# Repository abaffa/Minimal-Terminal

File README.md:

# Baffa Terminal (minimal-terminal clone) 

This is a Simple Terminal board based on "Minimal-Terminal" project by Carsten Herting (oct/2021 https://github.com/slu4coder/Minimal-Terminal).

Current version supports US-International keyboard mapping, four basic serial speeds (115200, 57600, 38400, 9600 BPS) and [supports some basic CSI/Ansi escapes](supported_escapes.md).
 
The prototype board has been tested with my CP/M machine (see http://baffa-2.baffasoft.com.br) but there is another board compatible with RC2014 pinout. 

### Video

## Baffa-2 Terminal Board:

[Order Baffa-2 Minimal Terminal PCB from PCBWay](https://www.pcbway.com/project/shareproject/Baffa_2_Minimal_Terminal_f85704c4.html)

## RC2014 Minimal-Terminal Module

[Order RC2014 Minimal Terminal PCB from PCBWay](https://www.pcbway.com/project/shareproject/RC2014_Minimal_Terminal_41593f8c.html)

## Bill of Materials

| Qty | Value | Parts | Description |
|:---:|:----------:|:-----|:-----|
| 1 |  PINHD-1X20 | JP4 |  PIN HEADER |
| 1 |  PINHD-1X40 | JP3 |  PIN HEADER |
| 6 |  100nf | C2, C6, C9, C10, C11, C12 | CAPACITOR |
| 2 |  10k | R10, R16 | RESISTOR |
| 1 | 150 | R13 | RESISTOR |
| 2 |  1k | R11, R12 | RESISTOR |
| 1 |  24Mhz XTAL |  XTAL |  XTAL SOCKET-14 |
| 1 |  330nf | C1 | CAPACITOR |
| 1 |  47uf | C7 | POLARIZED CAPACITOR |
| 1 |  74HC166N |  IC2 |  8-bit parallel load SHIFT REGISTER |
| 2 | 75 | R14, R15 | RESISTOR, American symbol |
| 1 |  7806T | IC1 |  Positive VOLTAGE REGULATOR |
| 2 |  ATMEGA328P-PU | UART_PS2, VGA |  PDIP-28 Atmel |
| 1 |  BUS UART | JP2 |  JUMPER |
| 1 |  MINI-DIN6PTH |  PS2_DIN |  mini DIN 6 Connector |
| 1 |  Power 9-12v | JP1 |  PIN HEADER |
| 1 |  RESET | S5 | MOM SWITCH |
| 1 |  SPEED | JP7 |  JUMPER |
| 1 | PINHD-1X6 | UART |  PIN HEADER |
| 1 | PINHD-1X6 |  VGA |  PIN HEADER |
| 1 | DSUB | VGA Output | SUB-D |
 
## License

Copyright (c) 2021 Augusto Baffa, Carsten Herting

Permission is hereby granted, free of charge, to any person obtaining a copy
of this software and associated documentation files (the "Software"), to deal
in the Software without restriction, including without limitation the rights
to use, copy, modify, merge, publish, distribute, sublicense, and/or sell
copies of the Software, and to permit persons to whom the Software is
furnished to do so, subject to the following conditions:

The above copyright notice and this permission notice shall be included in all
copies or substantial portions of the Software.

THE SOFTWARE IS PROVIDED "AS IS", WITHOUT WARRANTY OF ANY KIND, EXPRESS OR
IMPLIED, INCLUDING BUT NOT LIMITED TO THE WARRANTIES OF MERCHANTABILITY,
FITNESS FOR A PARTICULAR PURPOSE AND NONINFRINGEMENT. IN NO EVENT SHALL THE
AUTHORS OR COPYRIGHT HOLDERS BE LIABLE FOR ANY CLAIM, DAMAGES OR OTHER
LIABILITY, WHETHER IN AN ACTION OF CONTRACT, TORT OR OTHERWISE, ARISING FROM,
OUT OF OR IN CONNECTION WITH THE SOFTWARE OR THE USE OR OTHER DEALINGS IN THE
SOFTWARE.

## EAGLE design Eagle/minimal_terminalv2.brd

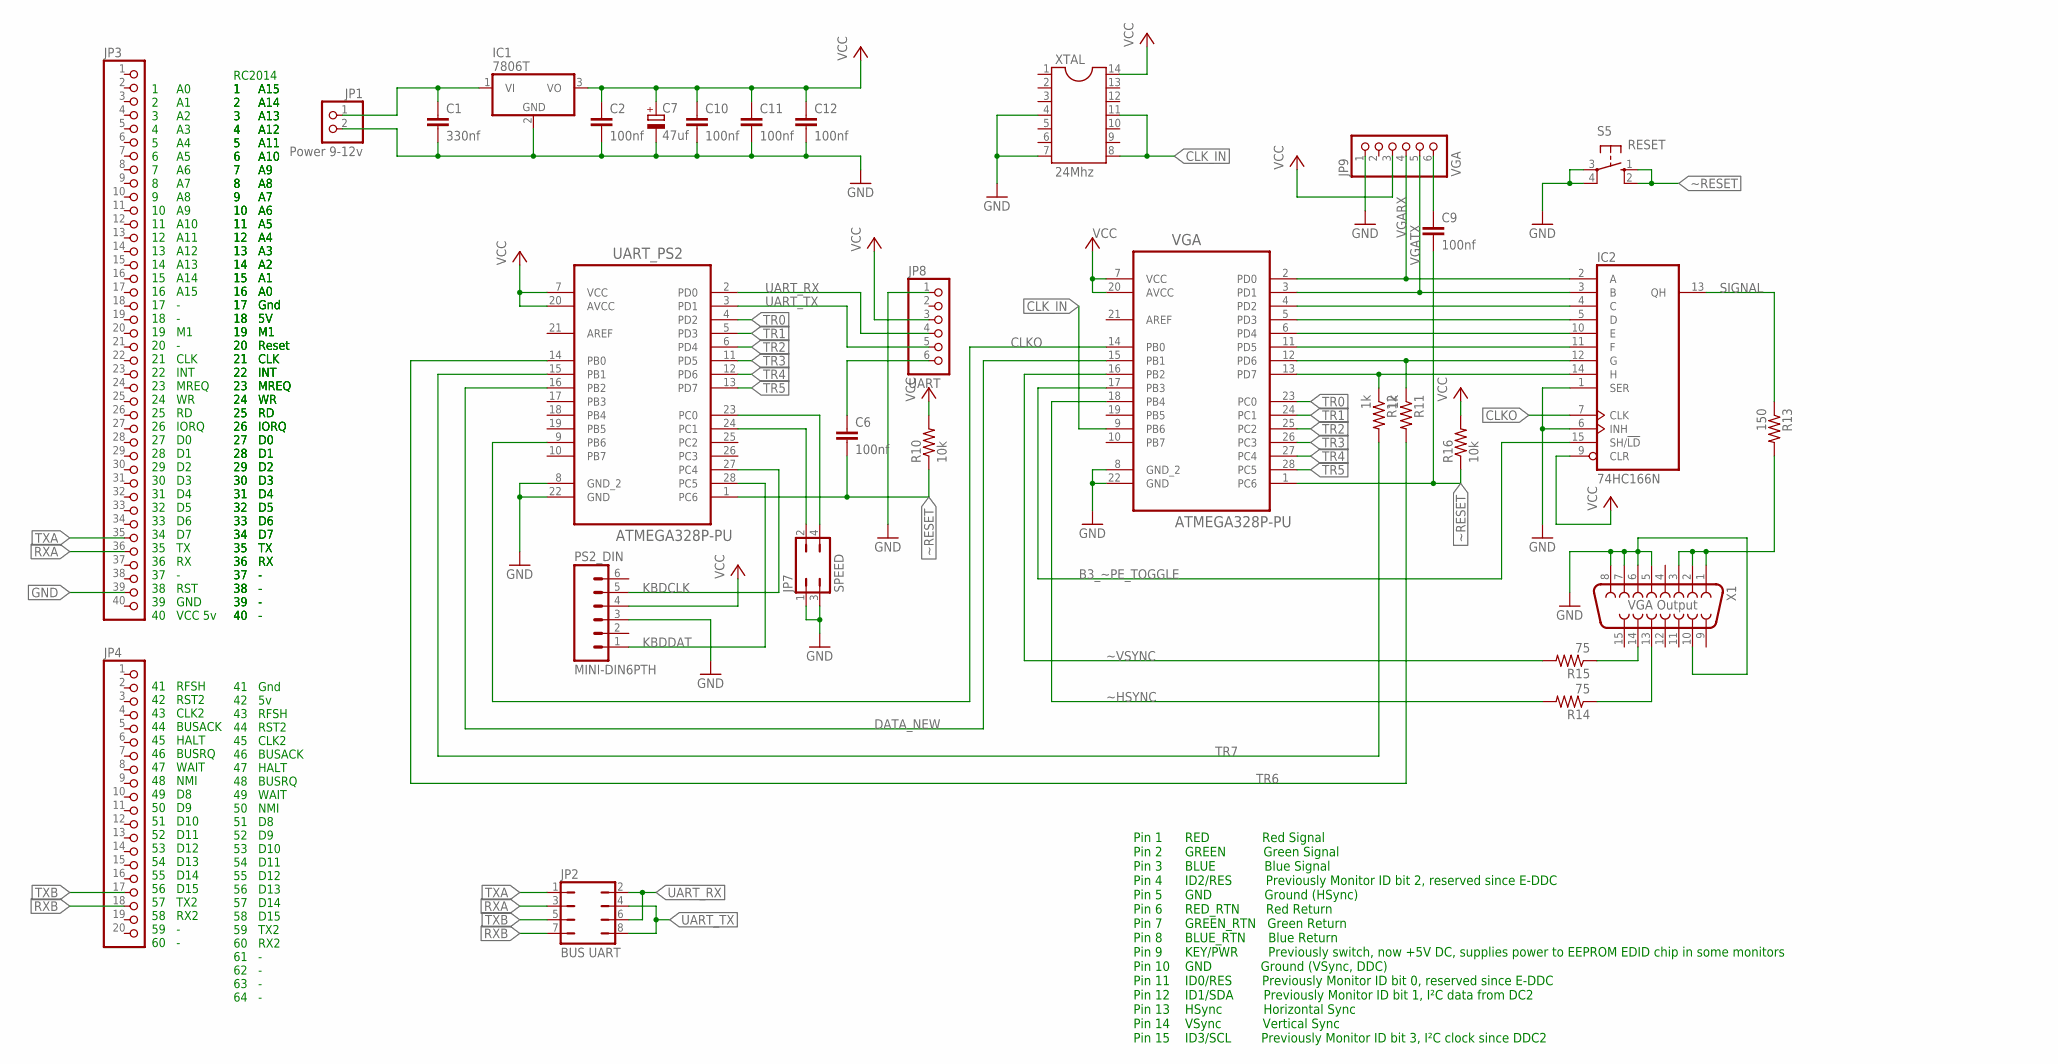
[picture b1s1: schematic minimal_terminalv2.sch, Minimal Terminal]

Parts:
C1: 330nf; C2.5-3
C2, C6, C9, C10, C11, C12: 100nf; C2.5-3
C7: 47uf; E2,5-6
IC1: 7806T; TO220H
IC2: 74HC166N; DIL16
JP1: Power 9-12v; 1X02
JP2: BUS UART; JP4Q
JP3: PINHD-1X40; 1X40
JP4: PINHD-1X20; 1X20
JP7: SPEED; JP2Q
JP8: UART; 1X06
JP9: VGA; 1X06
PS2_DIN: MINI-DIN6PTH; MINI-DIN6
R10, R16: 10k; 0204/7
R11, R12: 1k; 0204/7
R13: 150; 0204/7
R14, R15: 75; 0204/7
S5: RESET; B3F-10XX
UART_PS2: ATMEGA328P-PU; DIP254P762X457-28
VGA: ATMEGA328P-PU; DIP254P762X457-28
X1: VGA Output; HDF15H
XTAL: 24Mhz; SOCKET-14

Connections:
B3_~PE_TOGGLE: IC2.15 (SH/!LD), VGA.17 (PB3)
CLKO: IC2.7 (CLK), UART_PS2.9 (PB6), VGA.14 (PB0)
CLK_IN: VGA.9 (PB6), XTAL.8, XTAL.11
DATA_NEW: UART_PS2.16 (PB2), VGA.15 (PB1)
GND: C1.2, C2.2, C7.-, C10.2, C11.2, C12.2, IC1.2 (GND), IC2.1 (SER), IC2.6 (INH), IC2.8 (GND), JP1.2, JP3.39, JP7.1, JP7.3, JP8.1, JP9.1, PS2_DIN.3, S5.3, S5.4 (P1), UART_PS2.8 (GND_2), UART_PS2.22 (GND), VGA.8 (GND_2), VGA.22 (GND), X1.5, X1.6, X1.7, X1.8, X1.10, XTAL.4, XTAL.7
KBDCLK: PS2_DIN.5, UART_PS2.27 (PC4)
KBDDAT: PS2_DIN.1, UART_PS2.28 (PC5)
unnamed: C1.1, IC1.1 (VI), JP1.1
unnamed: C6.1, JP8.6
unnamed: JP7.2, UART_PS2.24 (PC1)
unnamed: JP7.4, UART_PS2.23 (PC0)
unnamed: IC2.12 (G), R11.1, VGA.12 (PD6)
unnamed: IC2.14 (H), R12.1, VGA.13 (PD7)
unnamed: IC2.4 (C), VGA.4 (PD2)
unnamed: IC2.5 (D), VGA.5 (PD3)
unnamed: IC2.10 (E), VGA.6 (PD4)
unnamed: IC2.11 (F), VGA.11 (PD5)
unnamed: R13.2, X1.1, X1.2, X1.3
unnamed: R14.1, X1.13
unnamed: R15.1, X1.14
unnamed: C9.1, JP9.6
RXA: JP2.3, JP3.36
RXB: JP2.7, JP4.18
SIGNAL: IC2.13 (QH), R13.1
TR0: UART_PS2.4 (PD2), VGA.23 (PC0)
TR1: UART_PS2.5 (PD3), VGA.24 (PC1)
TR2: UART_PS2.6 (PD4), VGA.25 (PC2)
TR3: UART_PS2.11 (PD5), VGA.26 (PC3)
TR4: UART_PS2.12 (PD6), VGA.27 (PC4)
TR5: UART_PS2.13 (PD7), VGA.28 (PC5)
TR6: R11.2, UART_PS2.14 (PB0)
TR7: R12.2, UART_PS2.15 (PB1)
TXA: JP2.1, JP3.35
TXB: JP2.5, JP4.17
UART_RX: JP2.2, JP2.6, JP8.4, UART_PS2.2 (PD0)
UART_TX: JP2.4, JP2.8, JP8.5, UART_PS2.3 (PD1)
VCC: C2.1, C7.+, C10.1, C11.1, C12.1, IC1.3 (VO), IC2.9 (CLR), IC2.16 (VCC), JP8.3, JP9.3, PS2_DIN.4, R10.2, R16.2, UART_PS2.7 (VCC), UART_PS2.20 (AVCC), VGA.7 (VCC), VGA.20 (AVCC), XTAL.14
VGARX: IC2.2 (A), JP9.4, VGA.2 (PD0)
VGATX: IC2.3 (B), JP9.5, VGA.3 (PD1)
~HSYNC: R14.2, VGA.18 (PB4)
~RESET: C6.2, C9.2, R10.1, R16.1, S5.1 (S), S5.2 (S1), UART_PS2.1 (PC6), VGA.1 (PC6)
~VSYNC: R15.2, VGA.16 (PB2)

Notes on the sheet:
Pin 1 RED Red Signal Pin 2 GREEN Green Signal Pin 3 BLUE Blue Signal Pin 4 ID2/RES Previously Monitor ID bit 2, reserved since E-DDC Pin 5 GND Ground (HSync) Pin 6 RED_RTN Red Return Pin 7 GREEN_RTN Green Return Pin 8 BLUE_RTN Blue Return Pin 9 KEY/PWR Previously switch, now +5V DC, supplies power 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
1 A0 2 A1 3 A2 4 A3 5 A4 6 A5 7 A6 8 A7 9 A8 10 A9 11 A10 12 A11 13 A12 14 A13 15 A14 16 A15 17 - 18 - 19 M1 20 - 21 CLK 22 INT 23 MREQ 24 WR 25 RD 26 IORQ 27 D0 28 D1 29 D2 30 D3 31 D4 32 D5 33 D6 34 D7 35 TX 36 RX 37 - 38 RST 39 GND 40 VCC 5v
41 RFSH 42 RST2 43 CLK2 44 BUSACK 45 HALT 46 BUSRQ 47 WAIT 48 NMI 49 D8 50 D9 51 D10 52 D11 53 D12 54 D13 55 D14 56 D15 57 TX2 58 RX2 59 - 60 -
1 A15 2 A14 3 A13 4 A12 5 A11 6 A10 7 A9 8 A8 9 A7 10 A6 11 A5 12 A4 13 A3 14 A2 15 A1 16 A0 17 Gnd 18 5V 19 M1 20 Reset 21 CLK 22 INT 23 MREQ 24 WR 25 RD 26 IORQ 27 D0 28 D1 29 D2 30 D3 31 D4 32 D5 33 D6 34 D7 35 TX 36 RX 37 - 38 - 39 - 40 -
RC2014 1 A15 2 A14 3 A13 4 A12 5 A11 6 A10 7 A9 8 A8 9 A7 10 A6 11 A5 12 A4 13 A3 14 A2 15 A1 16 A0 17 Gnd 18 5V 19 M1 20 Reset 21 CLK 22 INT 23 MREQ 24 WR 25 RD 26 IORQ 27 D0 28 D1 29 D2 30 D3 31 D4 32 D5 33 D6 34 D7 35 TX 36 RX 37 - 38 - 39 - 40 -
41 Gnd 42 5v 43 RFSH 44 RST2 45 CLK2 46 BUSACK 47 HALT 48 BUSRQ 49 WAIT 50 NMI 51 D8 52 D9 53 D10 54 D11 55 D12 56 D13 57 D14 58 D15 59 TX2 60 RX2 61 - 62 - 63 - 64 -

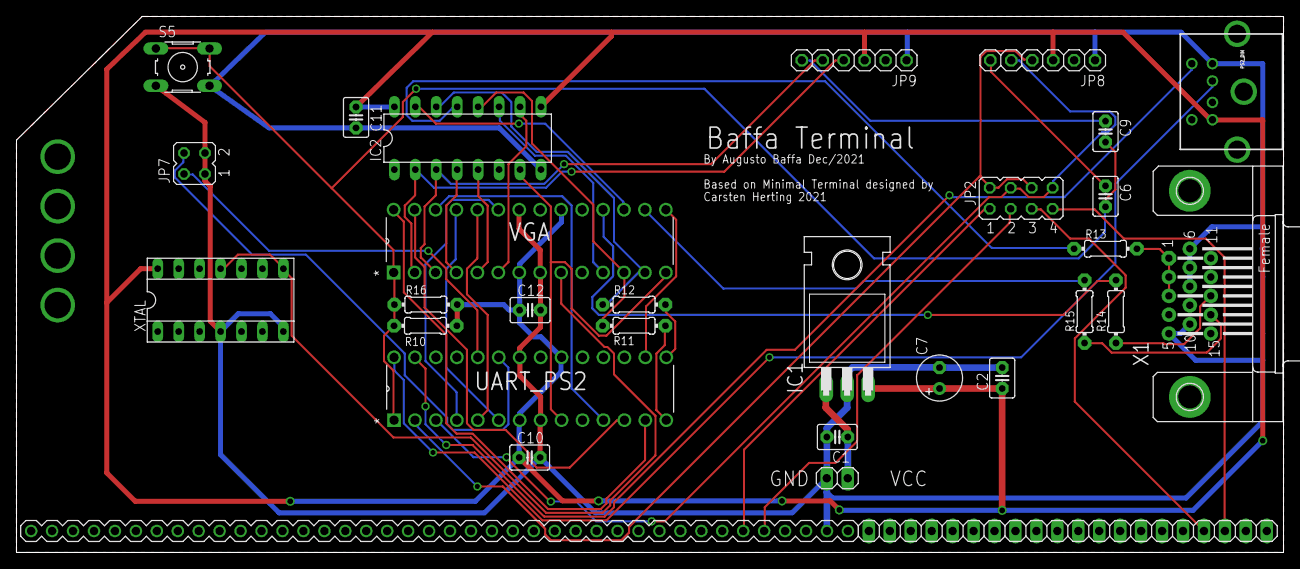
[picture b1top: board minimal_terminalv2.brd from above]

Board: 2 copper layers, 153.7 x 65.0 mm, 30 parts (0 on the bottom side), 42 nets.

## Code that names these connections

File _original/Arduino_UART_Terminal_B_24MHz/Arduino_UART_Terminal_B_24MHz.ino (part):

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// ***************************************************************************
// Pin C0-5: terminal input bits 0-5
// Pin D0-7: parallel pixel output to 74166, in between: D6-7 terminal input bits 6-7
// Pin B0:   CLKO ATmega328 system clock output
// Pin B1:   DATA_NEW input handshake
// Pin B2:   /VSYNC VGA (timer1, every 1/60s, could also be done)
// Pin B3:   /PE low pulse (by hand inside ISR for 74166 /PE pixel shift register sync parallel load)
// Pin B4:   /HSYNC VGA (by hand inside ISR, every 32µs)
// Pin B5:   DATA_ACK output handshake
// See license at the end of this file.

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  DDRD  = 0b11111111;               // PORTD is always output
  PORTD = 0b00000000;
  DDRB  = 0b00111100;               // B0-1: terminal input bits 0-1, B2: VSYNC (timer1), B3: 74165 /PL (timer2 or by hand???), B4: HSync by hand inside ISR
  PORTB = 0b00011000;               // HSYNC=1, /PE=1

  GTCCR = 0b10000011;               // set TSM, PSRSYNC und PSRASY to correlate all 3 timers

  // *****************************
  // ***** Timer0: VGA HSYNC *****
  // *****************************
  TCNT0  = 68;                       // align VSYNC and HSYNC pulses
  TCCR0A = (1 << WGM01) | (0 << WGM00);   // mode 2: Clear Timer on Compare Match (CTC)
  TCCR0B = (0 << WGM02) | (0 << CS02) | (1 << CS01) | (0 << CS00); // x8 prescaler -> 0.5µs
  OCR0A  = 95;                      // 95, 79, 16MHz: 63, compare match register A (TOP) -> 32µs
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
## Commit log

2021-12-31 . updating minimal terminal project
2021-12-31 Update README.md
    adding MIT license to Carsten Herting
2021-12-31 Create LICENSE
2022-01-02 . including RC2014 terminal version . margin adjust in README.md pics . adding scan_codes.xlsx
2022-01-06 . Adding Charmap table (char_map.xlsx) . Fixed '^' char bitmap to VGA . Added support to Caps Lock . Fixed Clear Screen CSI Escapes
2022-01-07 . added support to inverse escape ESC[{..}m . fixed inversed ^
2022-01-07 . add new fonts to char_map.xlsx and some chars in fixed default font
2022-01-08 . fixed minor bugs . added support to another escapes and escape parameters separeted by semicolon
2022-01-08 . added splash title on start up . fixed by in \e[1J where cursor at 0,0
2022-01-08 . fixed VGA bitmap for ` (was showing @) . fixed bug on escape \e[r;wH (screen position)
2022-01-08 . added # of lines to \e[#S and \e[#T
2022-01-08 . adding num lock support
2022-01-08 . updating eagle files with last fixes.
2022-01-09 . fixed ctrl \ (ibm layout keyboard with extra \ key between shift and z keys) . fixed ESC[J2 - must clear screen and set cursor position to 0,0
2022-02-20 . bit time fix in send command byte - it was causing problems with some keyboards
2022-05-28 . gerbers updated . added new images
2022-05-28 . adding schematics
2022-05-28 . updating README.md
2022-07-28 . adding apple 1 and apple ][ charmap
2022-07-29 adding prototype ugly pics :D

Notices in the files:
_original/Arduino_UART_Terminal_B_24MHz/Arduino_UART_Terminal_B_24MHz.ino:
Copyright (c) 2021 Carsten Herting
parts and their libraries:
SparkFun-Connectors: Licensing: Creative Commons ShareAlike 4.0 International - https://creativecommons.org/licenses/by-sa/4.0
